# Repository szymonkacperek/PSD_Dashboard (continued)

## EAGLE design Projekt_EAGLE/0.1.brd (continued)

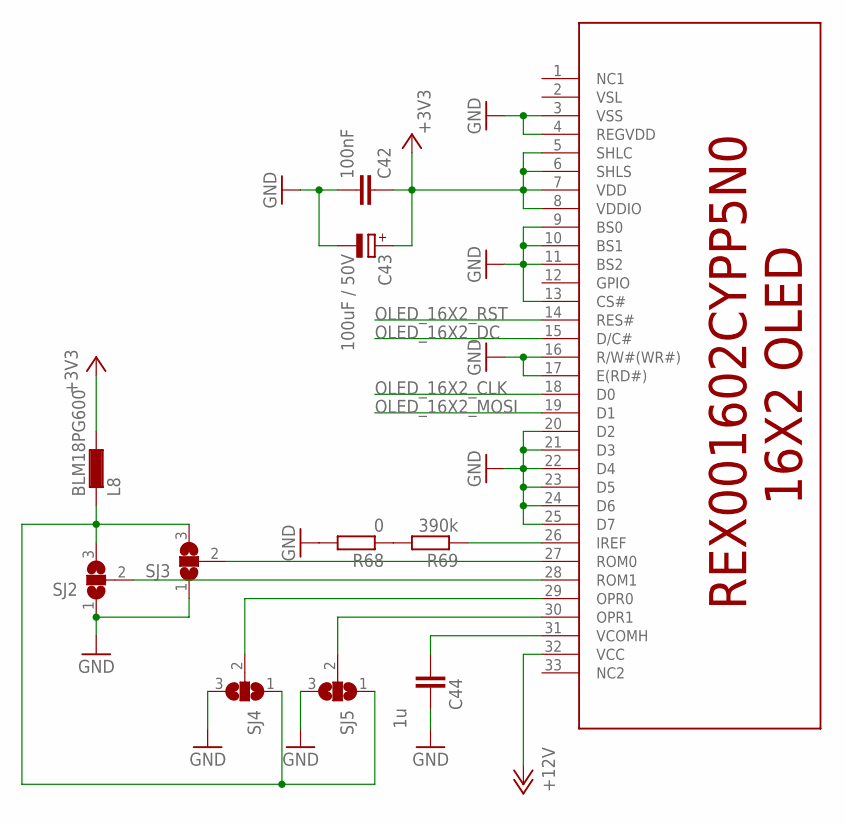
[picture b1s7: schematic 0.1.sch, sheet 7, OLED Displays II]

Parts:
C42: 100nF; C0805K
C43: 100uF / 50V; PANASONIC_F
C44: 1u; C0805K
DISPLAY1: REX001602CYPP5N0; 33PIN_LCD16X2
L8: BLM18PG600; L1608
R68: 0; R0805
R69: 390k; R0805
SJ2, SJ3, SJ4, SJ5: SJ2W; SJ_2

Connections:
+3V3: C42.1, C43.+, DISPLAY1.5 (SHLC), DISPLAY1.6 (SHLS), DISPLAY1.7 (VDD), DISPLAY1.8 (VDDIO), L8.1; also elsewhere on the board
+12V: DISPLAY1.32 (VCC); also elsewhere on the board
GND: C42.2, C43.-, C44.1, DISPLAY1.3 (VSS), DISPLAY1.4 (REGVDD), DISPLAY1.9 (BS0), DISPLAY1.10 (BS1), DISPLAY1.11 (BS2), DISPLAY1.13 (CS#), DISPLAY1.16 (R/W#(WR#)), DISPLAY1.17 (E(RD#)), DISPLAY1.20 (D2), DISPLAY1.21 (D3), DISPLAY1.22 (D4), DISPLAY1.23 (D5), DISPLAY1.24 (D6), DISPLAY1.25 (D7), R68.2, SJ2.1, SJ3.1, SJ4.3, SJ5.3; also elsewhere on the board
unnamed: DISPLAY1.26 (IREF), R69.1
unnamed: R68.1, R69.2
unnamed: DISPLAY1.27 (ROM0), SJ3.2
unnamed: DISPLAY1.28 (ROM1), SJ2.2
unnamed: C44.2, DISPLAY1.31 (VCOMH)
unnamed: L8.2, SJ2.3, SJ3.3, SJ4.1, SJ5.1
unnamed: DISPLAY1.30 (OPR1), SJ5.2
unnamed: DISPLAY1.29 (OPR0), SJ4.2
OLED_16X2_CLK: DISPLAY1.18 (D0); also elsewhere on the board
OLED_16X2_DC: DISPLAY1.15 (D/C#); also elsewhere on the board
OLED_16X2_MOSI: DISPLAY1.19 (D1); also elsewhere on the board
OLED_16X2_RST: DISPLAY1.14 (RES#); also elsewhere on the board

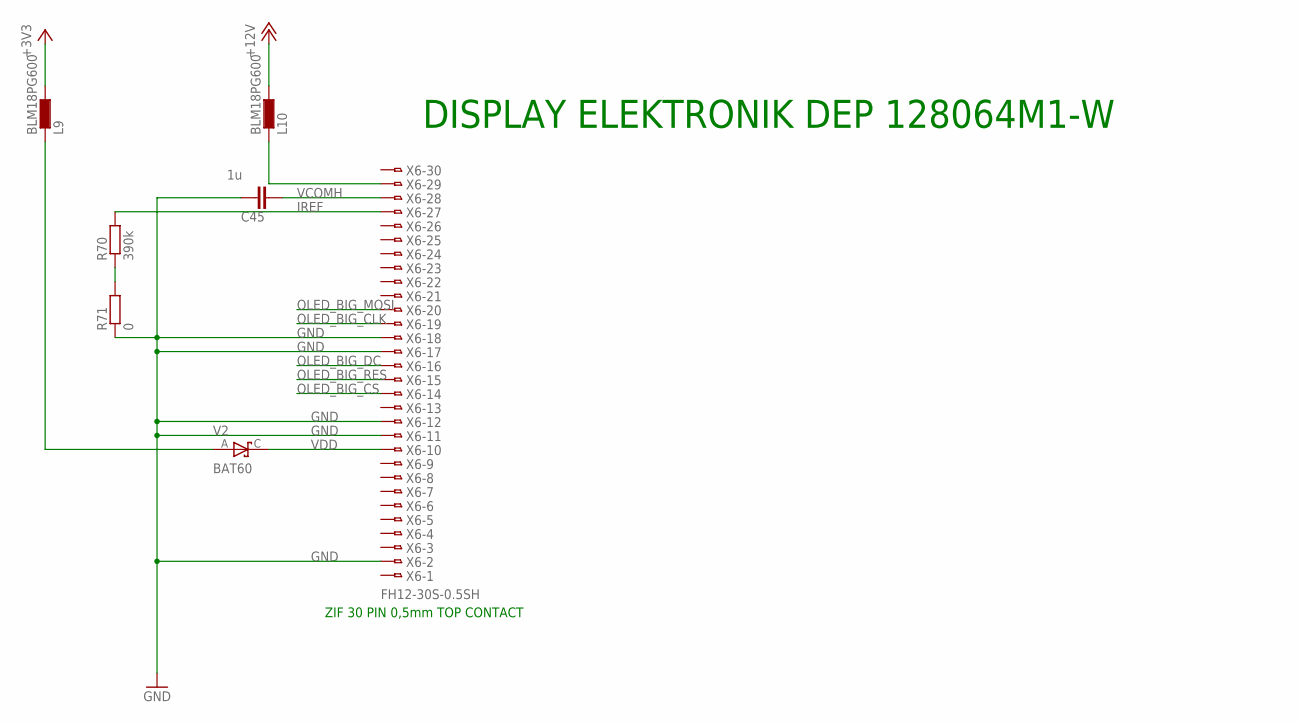
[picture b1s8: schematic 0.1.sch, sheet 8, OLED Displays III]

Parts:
C45: 1u; C0805K
L9, L10: BLM18PG600; L1608
R70: 390k; R0805
R71: 0; R0805
V2: BAT60; SOD323-R
X6: FH12-30S-0.5SH

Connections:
+3V3: L9.1; also elsewhere on the board
+12V: L10.1; also elsewhere on the board
GND: C45.1, R71.1, X6.2, X6.11, X6.12, X6.17, X6.18; also elsewhere on the board
IREF: R70.2, X6.27
unnamed: L10.2, X6.29
unnamed: L9.2, V2.A
unnamed: R70.1, R71.2
OLED_BIG_CLK: X6.19; also elsewhere on the board
OLED_BIG_CS: X6.14; also elsewhere on the board
OLED_BIG_DC: X6.16; also elsewhere on the board
OLED_BIG_MOSI: X6.20; also elsewhere on the board
OLED_BIG_RES: X6.15; also elsewhere on the board
VCOMH: C45.2, X6.28
VDD: V2.C, X6.10

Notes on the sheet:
DISPLAY ELEKTRONIK DEP 128064M1-W
ZIF 30 PIN 0,5mm TOP CONTACT

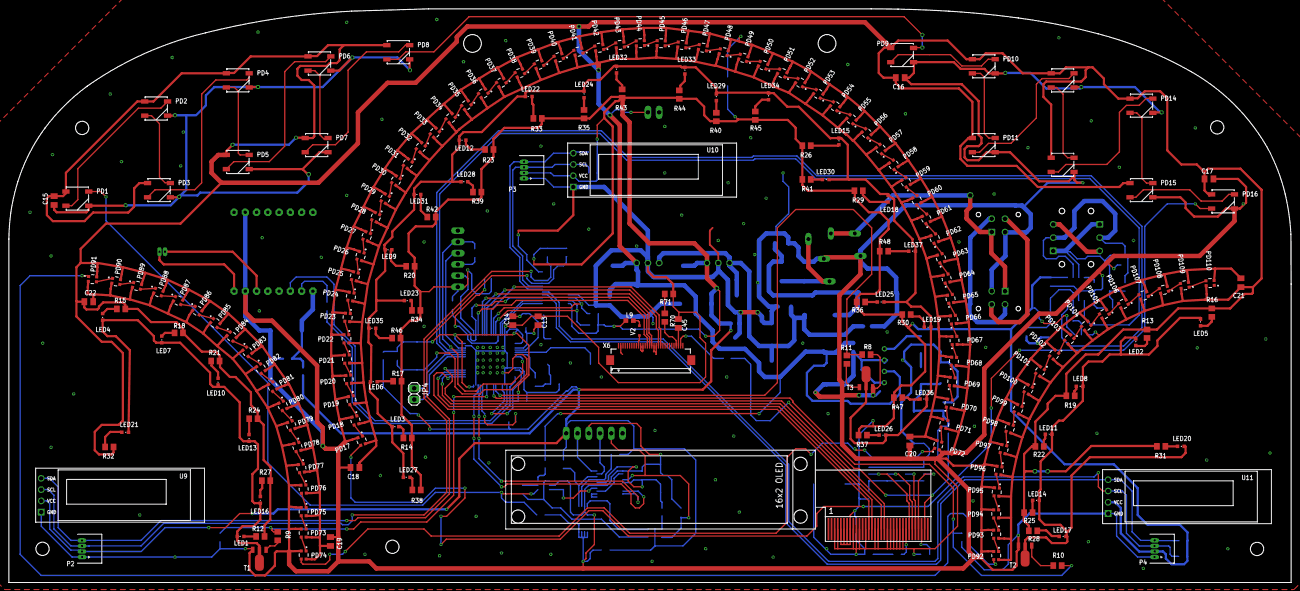
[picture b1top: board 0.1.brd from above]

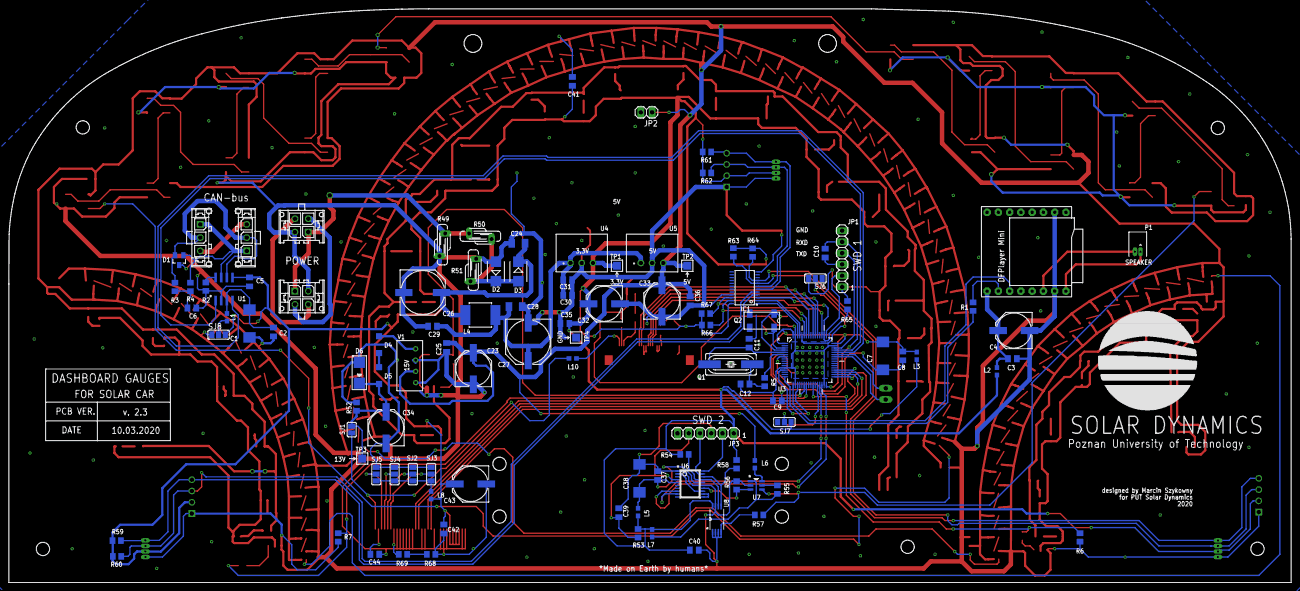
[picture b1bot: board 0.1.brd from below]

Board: 2 copper layers, 289.2 x 129.4 mm, 324 parts (109 on the bottom side), 245 nets.

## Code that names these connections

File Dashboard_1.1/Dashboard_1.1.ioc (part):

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Mcu.Name=STM32F103R(C-D-E)Tx
Mcu.Package=LQFP64
Mcu.UserName=STM32F103RETx
PA10.Mode=Asynchronous
PA10.Signal=USART1_RX
PA11.GPIOParameters=GPIO_PuPd
PA11.GPIO_PuPd=GPIO_PULLUP
PA11.Mode=Master
PA11.Signal=CAN_RX
PA12.Mode=Master
PA12.Signal=CAN_TX
PA13.Mode=Serial_Wire
PA13.Signal=SYS_JTMS-SWDIO
PA14.Mode=Serial_Wire
PA14.Signal=SYS_JTCK-SWCLK
PA2.Mode=Asynchronous
PA2.Signal=USART2_TX
PA3.Mode=Asynchronous
PA3.Signal=USART2_RX
PA6.Signal=S_TIM3_CH1
PA7.Signal=S_TIM3_CH2
PA9.Mode=Asynchronous
PA9.Signal=USART1_TX
PB0.Signal=S_TIM3_CH3
PB10.Mode=Asynchronous
PB10.Signal=USART3_TX
PB11.Mode=Asynchronous
PB11.Signal=USART3_RX
PB12.GPIOParameters=GPIO_Speed,PinState,GPIO_PuPd,GPIO_ModeDefaultOutputPP
PB12.GPIO_ModeDefaultOutputPP=GPIO_MODE_OUTPUT_PP
PB12.GPIO_PuPd=GPIO_NOPULL
PB12.GPIO_Speed=GPIO_SPEED_FREQ_LOW
PB12.PinState=GPIO_PIN_RESET
PB12.Signal=GPIO_Output
PB13.Mode=TX_Only_Simplex_Unidirect_Master
PB13.Signal=SPI2_SCK
PB14.GPIOParameters=GPIO_Speed,PinState,GPIO_PuPd,GPIO_ModeDefaultOutputPP
PB14.GPIO_ModeDefaultOutputPP=GPIO_MODE_OUTPUT_PP
PB14.GPIO_PuPd=GPIO_NOPULL
PB14.GPIO_Speed=GPIO_SPEED_FREQ_LOW
PB14.PinState=GPIO_PIN_RESET
PB14.Signal=GPIO_Output
PB15.Mode=TX_Only_Simplex_Unidirect_Master
PB15.Signal=SPI2_MOSI
PB3.Mode=TX_Only_Simplex_Unidirect_Master
PB3.Signal=SPI3_SCK
PB5.Mode=TX_Only_Simplex_Unidirect_Master
PB5.Signal=SPI3_MOSI
PB6.Mode=I2C
PB6.Signal=I2C1_SCL
PB7.Mode=I2C
PB7.Signal=I2C1_SDA
PB8.GPIOParameters=GPIO_Speed,PinState,GPIO_PuPd,GPIO_ModeDefaultOutputPP
PB8.GPIO_ModeDefaultOutputPP=GPIO_MODE_OUTPUT_PP
PB8.GPIO_PuPd=GPIO_NOPULL
PB8.GPIO_Speed=GPIO_SPEED_FREQ_LOW
PB8.PinState=GPIO_PIN_RESET
PB8.Signal=GPIO_Output
PB9.GPIOParameters=GPIO_Speed,PinState,GPIO_PuPd,GPIO_ModeDefaultOutputPP
PB9.GPIO_ModeDefaultOutputPP=GPIO_MODE_OUTPUT_PP
PB9.GPIO_PuPd=GPIO_NOPULL
PB9.GPIO_Speed=GPIO_SPEED_FREQ_LOW
PB9.PinState=GPIO_PIN_RESET
PB9.Signal=GPIO_Output
PC10.GPIOParameters=GPIO_Speed,PinState,GPIO_PuPd,GPIO_ModeDefaultOutputPP
PC10.GPIO_ModeDefaultOutputPP=GPIO_MODE_OUTPUT_PP
PC10.GPIO_PuPd=GPIO_NOPULL
PC10.GPIO_Speed=GPIO_SPEED_FREQ_LOW
PC10.PinState=GPIO_PIN_RESET
PC10.Signal=GPIO_Output
PC12.GPIOParameters=GPIO_Speed,PinState,GPIO_PuPd,GPIO_ModeDefaultOutputPP
PC12.GPIO_ModeDefaultOutputPP=GPIO_MODE_OUTPUT_PP
PC12.GPIO_PuPd=GPIO_NOPULL
PC12.GPIO_Speed=GPIO_SPEED_FREQ_LOW
PC12.PinState=GPIO_PIN_RESET
PC12.Signal=GPIO_Output
PC14-OSC32_IN.Mode=LSE-External-Oscillator
PC14-OSC32_IN.Signal=RCC_OSC32_IN
PC15-OSC32_OUT.Mode=LSE-External-Oscillator
PC15-OSC32_OUT.Signal=RCC_OSC32_OUT
PD0-OSC_IN.Mode=HSE-External-Oscillator
PD0-OSC_IN.Signal=RCC_OSC_IN
PD1-OSC_OUT.Mode=HSE-External-Oscillator
PD1-OSC_OUT.Signal=RCC_OSC_OUT
PD2.GPIOParameters=GPIO_Speed,PinState,GPIO_PuPd,GPIO_ModeDefaultOutputPP
PD2.GPIO_ModeDefaultOutputPP=GPIO_MODE_OUTPUT_PP
PD2.GPIO_PuPd=GPIO_NOPULL
PD2.GPIO_Speed=GPIO_SPEED_FREQ_LOW
PD2.PinState=GPIO_PIN_RESET
PD2.Signal=GPIO_Output
RCC.HSEDivPLL=RCC_HSE_PREDIV_DIV2
RCC.HSE_VALUE=16000000
RCC.SYSCLKFreq_VALUE=72000000
RCC.SYSCLKSource=RCC_SYSCLKSOURCE_PLLCLK
board=custom

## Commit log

2020-07-21 Wgrany program testowy
2020-07-24 Poprawka vol. 2
2020-07-24 Poprawka vol. 3
2020-07-24 Poprawka
2020-07-24 poprawka vol. 5
2020-07-24 poprawka vol. 6
2020-07-24 SWD wchodzi w konflikt z SPI3. Wylaczony CAN
2020-08-05 Dostepne sa juz pliki .hex lub .bin do wgrania na procesor w obu projektach.
2020-08-06 Dodany opis projektu w pliku .PDF
2020-08-10 dodane komentarze, poprawiona stylistyka
2020-08-10 Uaktualniony schemat EAGLE.
2020-08-11 Wlaczony UART3 do komunikacji z F030
2020-10-16 Wersja gotowa do testow. Wlaczone wszystkie wyswietlacze.
